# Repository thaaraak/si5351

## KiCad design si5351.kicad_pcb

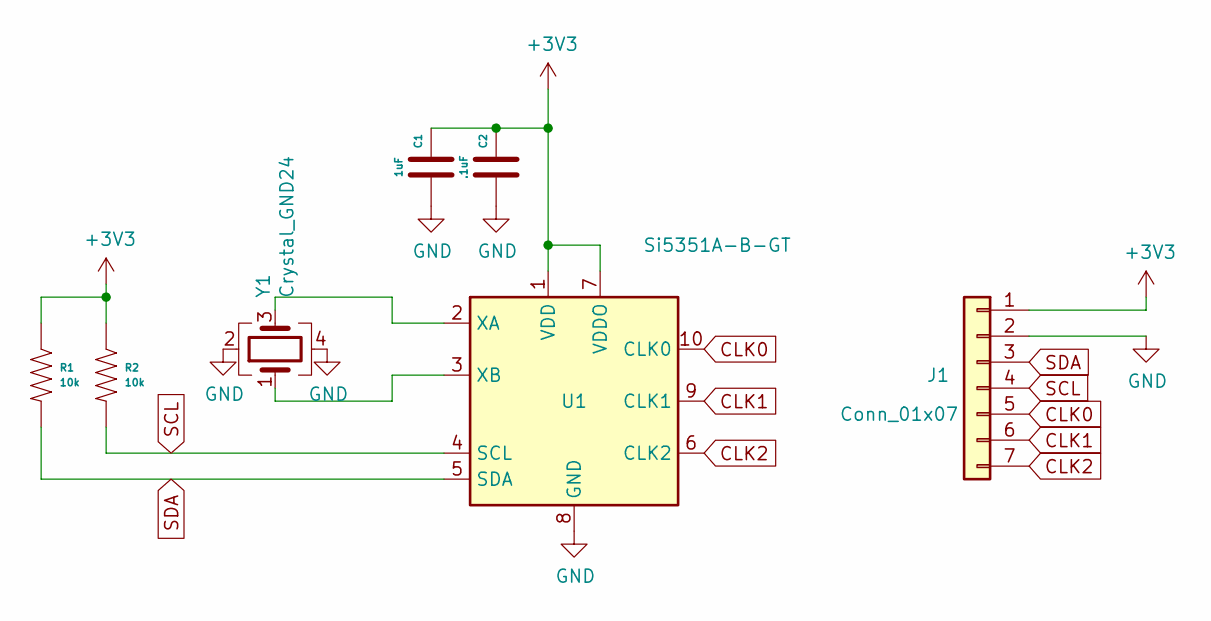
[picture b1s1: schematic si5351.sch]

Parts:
C1: 1uF; Capacitor 1206
C2: .1uF; Capacitor 1206
J1: Conn_01x07; PinHeader_1x07_P2.54mm_Vertical
R1, R2: 10k; Resistor 1206
U1: Si5351A-B-GT; MSOP-10_3x3mm_P0.5mm
Y1: Crystal_GND24; Crystal_SMD_Abracon_ABM8G-4Pin_3.2x2.5mm

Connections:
+3V3: C1.1, C2.1, J1.1, R1.1, R2.1, U1.1 (VDD), U1.7 (VDDO)
CLK0: J1.5, U1.10 (CLK0)
CLK1: J1.6, U1.9 (CLK1)
CLK2: J1.7, U1.6 (CLK2)
GND: C1.2, C2.2, J1.2, U1.8 (GND), Y1.2, Y1.4
unnamed: U1.2 (XA), Y1.3
unnamed: U1.3 (XB), Y1.1
SCL: J1.4, R2.2, U1.4 (SCL)
SDA: J1.3, R1.2, U1.5 (SDA)

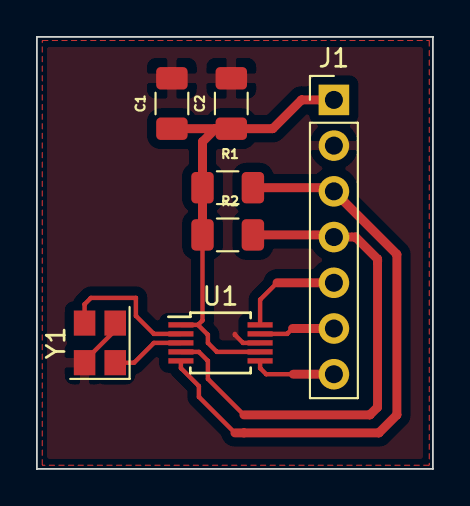
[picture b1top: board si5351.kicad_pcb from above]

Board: 2 copper layers, 22.0 x 24.0 mm, 7 parts (0 on the bottom side), 9 nets.

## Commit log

2022-11-09 added caps
2022-11-09 updated gerber
